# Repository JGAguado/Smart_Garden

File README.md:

[![Documentation Status][documentation-shield]][documentation]
[![GitHub Release][releases-shield]][releases]
[![License][license-shield]](LICENSE)
[![BuyIt][buyit-shield]][tindie]

[![Project Maintenance][maintenance-shield]][maintenance]
[![BuyMeCoffee][buymecoffee-shield]][buymecoffee]

# Smart Garden
The Smart Garden is an electronic board based on the ESP32 capable of controlling a combination of 4 irrigation valves and/or water pumps, 
supporting AC & DC voltages

## Project tree
---
<li><a href="./Design/">Design</a></li>
<li><a href="./Documentation/">Documentation</a></li>

<li><a href="./README.md">README.md</a></li>

[documentation-shield]: https://readthedocs.org/projects/smart-garden/badge/?version=latest&style=for-the-badge
[documentation]: https://smart-garden.readthedocs.io/en/latest/

[releases-shield]: https://img.shields.io/github/release/JGAguado/Smart_Garden.svg?style=for-the-badge
[releases]: https://github.com/JGAguado/Smart_Garden/releases

[license-shield]: https://img.shields.io/badge/License-CC%20BY--NC--SA%204.0-lightgrey.svg?style=for-the-badge

[maintenance-shield]: https://img.shields.io/badge/maintainer-J.%20G.%20Aguado-blue.svg?style=for-the-badge
[maintenance]: https://github.com/JGAguado

[buymecoffee-shield]: https://img.shields.io/badge/buy%20me%20a%20coffee-support-yellow.svg?style=for-the-badge
[buymecoffee]: https://www.buymeacoffee.com/J.G.Aguado

[buyit-shield]: https://img.shields.io/badge/get%20it%20on-tindie-247d84.svg?style=for-the-badge
[tindie]: https://www.tindie.com/products/jgaguado/smart-garden/

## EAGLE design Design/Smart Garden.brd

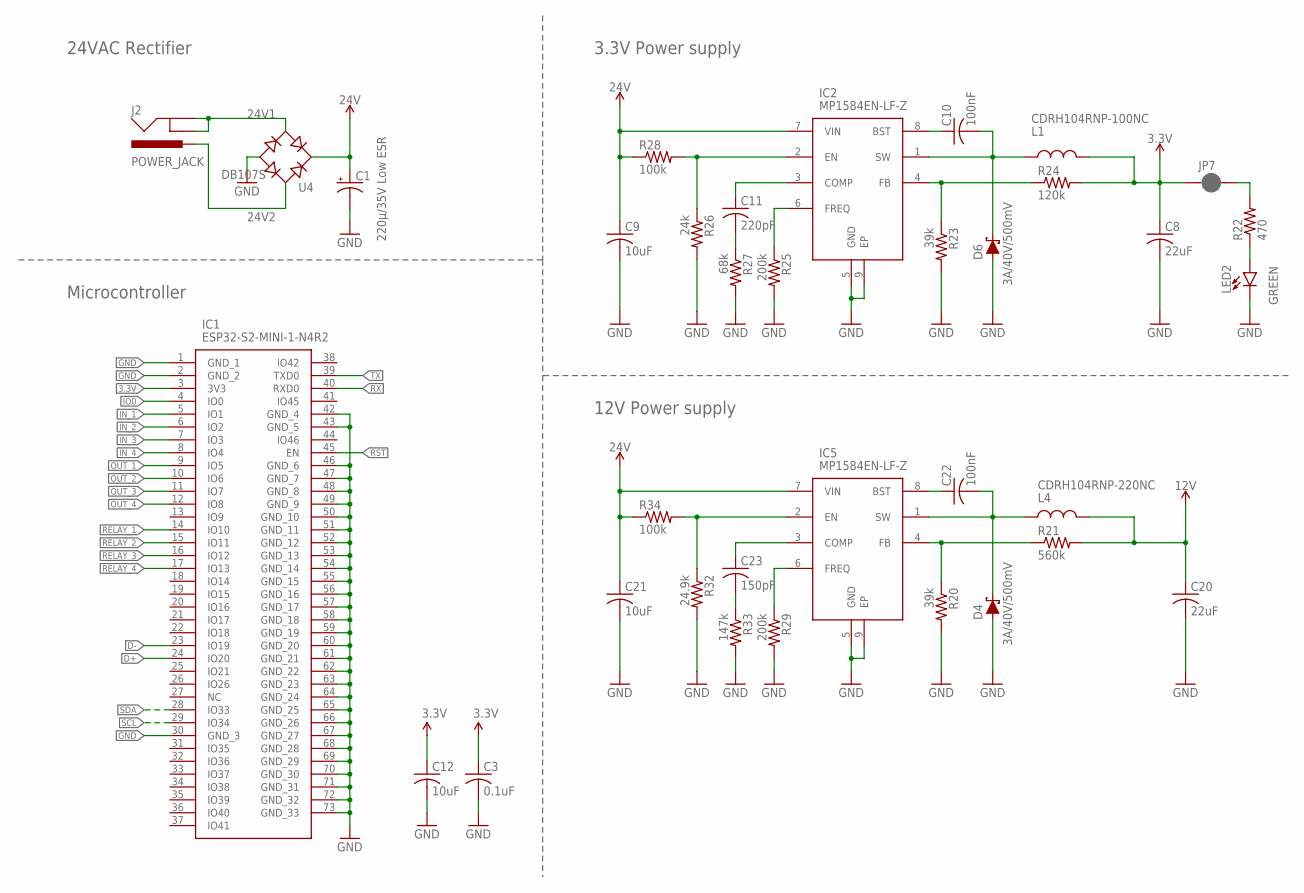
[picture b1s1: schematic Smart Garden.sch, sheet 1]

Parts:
C1: 220µ/35V Low ESR; PANASONIC_F
C3: 0.1uF; C0603
C8: 22uF; C0603
C9, C12: 10uF; C0603
C10: 100nF; C0603
C11: 220pF; C0603
C20: 22uF; 0603
C21: 10uF; 0603
C22: 100nF; 0603
C23: 150pF; 0603
D4, D6: 3A/40V/500mV; SMA-DIODE
IC1: ESP32-S2-MINI-1-N4R2; ESP32S2MINI1N4R2
IC2, IC5: MP1584EN-LF-Z; SOIC127P600X170-9N
J2: POWER_JACK; POWER_JACK_PTH
JP7: JUMPER-SMT_2_NC_PASTE_NO-SILK; SMT-JUMPER_2_NC_PASTE_NO-SILK
L1: CDRH104RNP-100NC; CDRH104RNP
L4: CDRH104RNP-220NC; CDRH104RNP
LED2: GREEN; LED-0603; LCSC C72043
R20: 39k; 0603
R21: 560k; 0603
R22: 470; R0603
R23: 39k; R0603
R24: 120k; R0603
R25: 200k; R0603
R26: 24k; R0603
R27: 68k; R0603
R28: 100k; R0603
R29: 200k; 0603
R32: 24.9k; 0603
R33: 147k; 0603
R34: 100k; 0603
U4: DB107S; DBS; LCSC C5377

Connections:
3.3V: C3.1, C8.1, C12.1, IC1.3 (3V3), JP7.1, L1.2, R24.2; also elsewhere on the board
12V: C20.1, L4.2, R21.2; also elsewhere on the board
24V: C1.+, C9.1, C21.1, IC2.7 (VIN), IC5.7 (VIN), R28.1, R34.1, U4.+
24V1: J2.GND, J2.GNDBREAK, U4.AC2; also elsewhere on the board
24V2: J2.PWR, U4.AC1; also elsewhere on the board
D+: IC1.24 (IO20); also elsewhere on the board
D-: IC1.23 (IO19); also elsewhere on the board
GND: C1.-, C3.2, C8.2, C9.2, C12.2, C20.2, C21.2, D4.A, D6.A, IC1.1 (GND_1), IC1.2 (GND_2), IC1.30 (GND_3), IC1.42 (GND_4), IC1.43 (GND_5), IC1.46 (GND_6), IC1.47 (GND_7), IC1.48 (GND_8), IC1.49 (GND_9), IC1.50 (GND_10), IC1.51 (GND_11), IC1.52 (GND_12), IC1.53 (GND_13), IC1.54 (GND_14), IC1.55 (GND_15), IC1.56 (GND_16), IC1.57 (GND_17), IC1.58 (GND_18), IC1.59 (GND_19), IC1.60 (GND_20), IC1.61 (GND_21), IC1.62 (GND_22), IC1.63 (GND_23), IC1.64 (GND_24), IC1.65 (GND_25), IC1.66 (GND_26), IC1.67 (GND_27), IC1.68 (GND_28), IC1.69 (GND_29), IC1.70 (GND_30), IC1.71 (GND_31), IC1.72 (GND_32), IC1.73 (GND_33), IC2.5 (GND), IC2.9 (EP), IC5.5 (GND), IC5.9 (EP), LED2.C, R20.2, R23.2, R25.2, R26.2, R27.2, R29.2, R32.2, R33.2, U4.-; also elsewhere on the board
IN_1: IC1.5 (IO1); also elsewhere on the board
IN_2: IC1.6 (IO2); also elsewhere on the board
IN_3: IC1.7 (IO3); also elsewhere on the board
IN_4: IC1.8 (IO4); also elsewhere on the board
IO0: IC1.4 (IO0); also elsewhere on the board
unnamed: JP7.2, R22.2
unnamed: C22.1, IC5.8 (BST)
unnamed: C22.2, D4.C, IC5.1 (SW), L4.1
unnamed: LED2.A, R22.1
unnamed: C10.1, IC2.8 (BST)
unnamed: C10.2, D6.C, IC2.1 (SW), L1.1
unnamed: IC2.4 (FB), R23.1, R24.1
unnamed: C11.2, R27.1
unnamed: C11.1, IC2.3 (COMP)
unnamed: IC2.6 (FREQ), R25.1
unnamed: IC2.2 (EN), R26.1, R28.2
unnamed: IC5.4 (FB), R20.1, R21.1
unnamed: C23.2, R33.1
unnamed: C23.1, IC5.3 (COMP)
unnamed: IC5.6 (FREQ), R29.1
unnamed: IC5.2 (EN), R32.1, R34.2
OUT_1: IC1.9 (IO5); also elsewhere on the board
OUT_2: IC1.10 (IO6); also elsewhere on the board
OUT_3: IC1.11 (IO7); also elsewhere on the board
OUT_4: IC1.12 (IO8); also elsewhere on the board
RELAY_1: IC1.14 (IO10); also elsewhere on the board
RELAY_2: IC1.15 (IO11); also elsewhere on the board
RELAY_3: IC1.16 (IO12); also elsewhere on the board
RELAY_4: IC1.17 (IO13); also elsewhere on the board
RST: IC1.45 (EN); also elsewhere on the board
RX: IC1.40 (RXD0); also elsewhere on the board
SCL: IC1.29 (IO34); also elsewhere on the board
SDA: IC1.28 (IO33); also elsewhere on the board
TX: IC1.39 (TXD0); also elsewhere on the board

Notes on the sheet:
Microcontroller
24VAC Rectifier
3.3V Power supply
12V Power supply

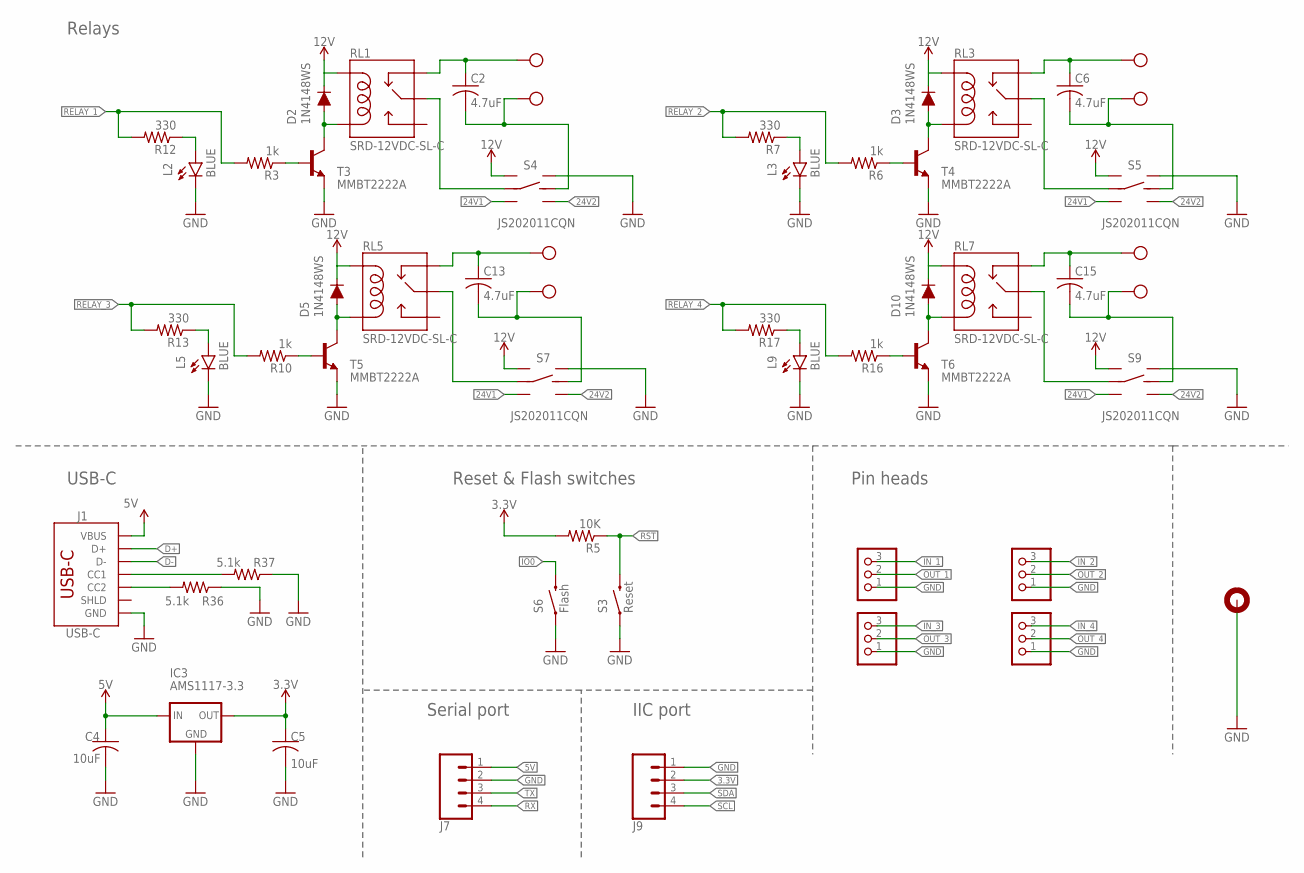
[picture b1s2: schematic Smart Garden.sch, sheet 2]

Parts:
C2, C6, C13, C15: 4.7uF; C1206; LCSC C29823
C4, C5: 10uF; C0603
D2, D3, D5, D10: 1N4148WS; SOD-323
H1: 92X84; 92X87
IC3: AMS1117-3.3; SOT223
J1: USB-C; USB-C-16P-4LAYER-ISOLATED
J7, J9: CONN_04PTH; 1X04
JP2, JP3, JP4, JP5: PINHD-1X3; 1X03
L2, L3, L5, L9: BLUE; LED-0603
R3, R6, R10, R16: 1k; R0603; LCSC C22843
R5: 10K; R0603
R7, R12, R13, R17: 330; R0603
R36, R37: 5.1k; R0603
RL1, RL3, RL5, RL7: SRD-12VDC-SL-C; SRD-05VDC-SL-C
S3: Reset; TACTILE_SWITCH_SMD_5.2MM
S4, S5, S7, S9: JS202011CQN; DPDT_JS202011CQN
S6: Flash; TACTILE_SWITCH_SMD_5.2MM
T3, T4, T5, T6: MMBT2222A; SOT23; LCSC C8512
X2, X4, X6, X7: W237-102

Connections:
3.3V: C5.1, IC3.2 (OUT), J9.2, R5.2; also elsewhere on the board
5V: C4.1, IC3.3 (IN), J1.VBUS1 (VBUS), J1.VBUS2 (VBUS), J7.1
12V: D2.C, D3.C, D5.C, D10.C, RL1.COIL1, RL3.COIL1, RL5.COIL1, RL7.COIL1, S4.1 (L1), S5.1 (L1), S7.1 (L1), S9.1 (L1); also elsewhere on the board
24V1: S4.3 (L2), S5.3 (L2), S7.3 (L2), S9.3 (L2); also elsewhere on the board
24V2: S4.6 (R2), S5.6 (R2), S7.6 (R2), S9.6 (R2); also elsewhere on the board
CC3: J1.B5 (CC2), R36.2
CC4: J1.A5 (CC1), R37.2
D+: J1.A6 (D+), J1.B6 (D+); also elsewhere on the board
D-: J1.A7 (D-), J1.B7 (D-); also elsewhere on the board
GND: C4.2, C5.2, H1.B3,1, H1.B3,2, H1.B3,3, H1.B3,6, H1.P$1, H1.P$2, H1.P$3, H1.P$4, H1.P$5, H1.P$6, H1.P$7, H1.P$8, H1.P$9, H1.P$10, H1.P$11, H1.P$12, H1.P$13, H1.P$14, H1.P$15, H1.P$16, H1.P$17, H1.P$18, H1.P$19, H1.P$20, H1.P$21, H1.P$22, H1.P$23, H1.P$24, H1.P$25, H1.P$26, H1.P$27, H1.P$28, H1.P$29, H1.P$30, H1.P$31, H1.P$32, IC3.1 (GND), J1.GND, J1.GND2 (GND), J7.2, J9.1, JP2.1, JP3.1, JP4.1, JP5.1, L2.C, L3.C, L5.C, L9.C, R36.1, R37.1, S3.1, S4.4 (R1), S5.4 (R1), S6.1, S7.4 (R1), S9.4 (R1), T3.2 (E), T4.2 (E), T5.2 (E), T6.2 (E); also elsewhere on the board
IN_1: JP5.3; also elsewhere on the board
IN_2: JP4.3; also elsewhere on the board
IN_3: JP3.3; also elsewhere on the board
IN_4: JP2.3; also elsewhere on the board
IO0: S6.3 (2); also elsewhere on the board
unnamed: RL1.SWCOMMON, S4.2 (LC)
unnamed: C2.2, S4.5 (RC), X7.2
unnamed: C2.1, RL1.SWCLOSED (SWCLOSE), X7.1
unnamed: D2.A, RL1.COIL0, T3.3 (C)
unnamed: R3.1, T3.1 (B)
unnamed: D3.A, RL3.COIL0, T4.3 (C)
unnamed: R6.1, T4.1 (B)
unnamed: L3.A, R7.1
unnamed: RL3.SWCOMMON, S5.2 (LC)
unnamed: C6.2, S5.5 (RC), X2.2
unnamed: C6.1, RL3.SWCLOSED (SWCLOSE), X2.1
unnamed: L2.A, R12.1
unnamed: D5.A, RL5.COIL0, T5.3 (C)
unnamed: R10.1, T5.1 (B)
unnamed: L5.A, R13.1
unnamed: RL5.SWCOMMON, S7.2 (LC)
unnamed: C13.2, S7.5 (RC), X4.2
unnamed: C13.1, RL5.SWCLOSED (SWCLOSE), X4.1
unnamed: D10.A, RL7.COIL0, T6.3 (C)
unnamed: R16.1, T6.1 (B)
unnamed: L9.A, R17.1
unnamed: RL7.SWCOMMON, S9.2 (LC)
unnamed: C15.2, S9.5 (RC), X6.2
unnamed: C15.1, RL7.SWCLOSED (SWCLOSE), X6.1
OUT_1: JP5.2; also elsewhere on the board
OUT_2: JP4.2; also elsewhere on the board
OUT_3: JP3.2; also elsewhere on the board
OUT_4: JP2.2; also elsewhere on the board
RELAY_1: R3.2, R12.2; also elsewhere on the board
RELAY_2: R6.2, R7.2; also elsewhere on the board
RELAY_3: R10.2, R13.2; also elsewhere on the board
RELAY_4: R16.2, R17.2; also elsewhere on the board
RST: R5.1, S3.3 (2); also elsewhere on the board
RX: J7.4; also elsewhere on the board
SCL: J9.4; also elsewhere on the board
SDA: J9.3; also elsewhere on the board
TX: J7.3; also elsewhere on the board

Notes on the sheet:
Relays
USB-C
Pin heads
Reset & Flash switches
Serial port
IIC port

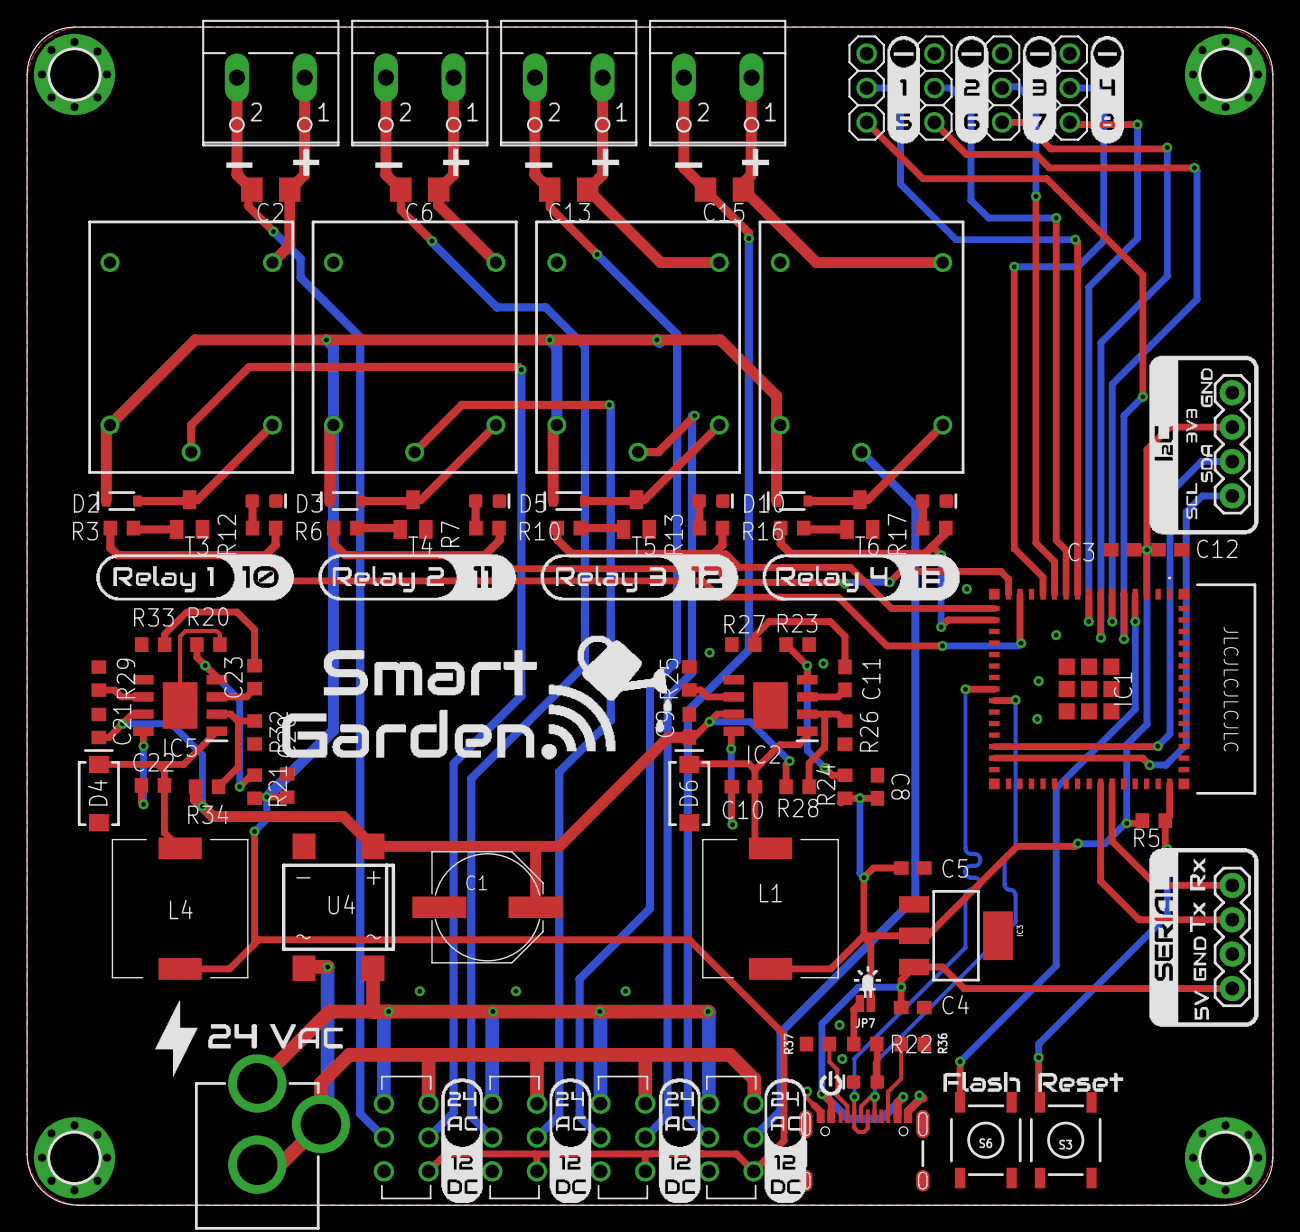
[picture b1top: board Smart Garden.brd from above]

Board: 2 copper layers, 92.0 x 87.0 mm, 87 parts (0 on the bottom side), 69 nets.

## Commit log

2022-04-13 Added silkscreen designs
2022-04-13 Added design files
2022-04-13 Added documentation
2022-04-24 Removed dimension drawings from brd and reloaded images
2022-05-11 Updated documentation adding Measures.pdf and Datasheets
2022-08-09 First commit to the CP2102 branch with schematic and a first layout of the CP2102
2022-08-20 First commit to the CP2102 branch
2022-09-26 Updated design files
2022-09-26 Updated documentation files
2022-10-06 Updated Silkscreen
2022-10-23 Updated Documentation/Images
2022-11-01 docs
2022-11-08 Updated Images
2023-02-05 docs/requirements.txt
2023-02-23 Silkscreen fixed
2023-03-15 Updated configuration.yaml
2024-07-02 Added V2R1 design files
2024-07-02 Added Silkscreen
2024-07-02 Images
2024-07-03 schematics
2024-07-07 Updated image
2024-08-05 First draft

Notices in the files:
parts and their libraries:
SparkFun-Connectors: Licensing: Creative Commons ShareAlike 4.0 International - https://creativecommons.org/licenses/by-sa/4.0
